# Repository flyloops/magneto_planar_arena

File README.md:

# magneto_planar_arena 
PCB Design for planar, five panel, arena for use with the magneto-tether rig.

* [Schematic (PDF)](planar_arena.pdf)
* [Bill-of-materials](BOM.txt)

# Top View: 

# Bottom View:

# License: 
Creative Commons Attribution 4.0 International CC BY 4.0

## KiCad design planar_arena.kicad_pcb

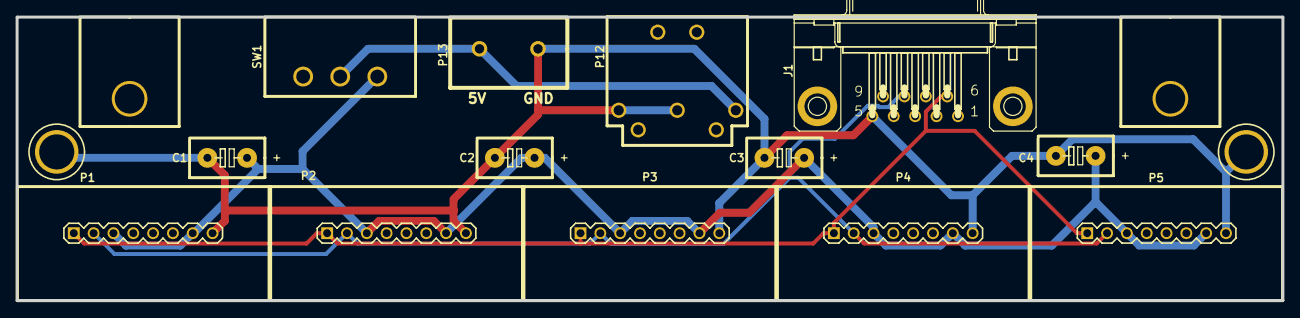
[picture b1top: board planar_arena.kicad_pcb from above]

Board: 2 copper layers, 162.2 x 36.3 mm, 17 parts (0 on the bottom side), 5 nets.

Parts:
C1, C2, C3, C4: 10uF; JFRC_Capacitor_Polarized
H1, H2: thru_hole_8-32; THRU_HOLE_8-32
J1: DB9; DB9_M09
M1, M2: BRACKET_6-32
P1, P2, P3, P4, P5: CONN_8; JFRC_1X08
P12: DIN_5; JFRC_DIN5-TH
P13: CONN_2; TERM_7P5MM
SW1: SWITCH_INV; slide_switch

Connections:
/5V: C1.1, C2.1, C3.1, C4.1, P1.3, P1.7, P2.3, P2.7, P3.3, P3.7, P4.3, P4.7, P5.3, P5.7, SW1.1
/5V_Supply: P12.3, P13.1, SW1.2
/SCL0: J1.6, P1.1, P2.1, P3.1, P4.1, P5.1
/SDA0: J1.8, P1.2, P2.2, P3.2, P4.2, P5.2
GND: C1.2, C2.2, C3.2, C4.2, H1.1, H2.1, J1.5, P1.8, P2.8, P3.8, P4.8, P5.8, P12.1, P12.2, P13.2

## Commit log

2018-03-09 Project creation.
2018-03-09 Updated images to larger versions.
2018-03-21 Updated bill of materials.
